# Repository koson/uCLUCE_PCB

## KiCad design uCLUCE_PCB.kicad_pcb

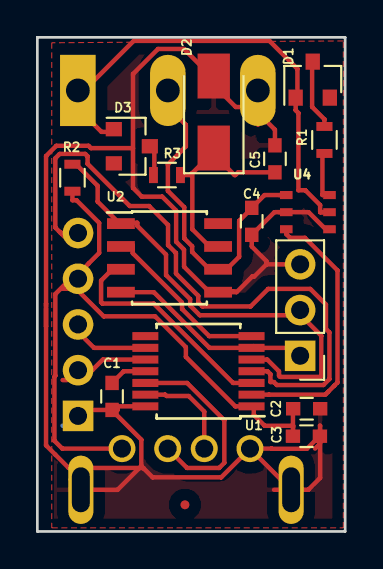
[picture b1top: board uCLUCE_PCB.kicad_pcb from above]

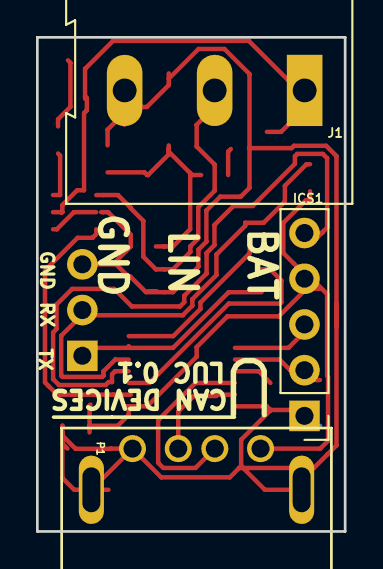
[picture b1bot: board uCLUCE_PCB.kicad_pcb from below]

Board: 2 copper layers, 17.1 x 27.5 mm, 19 parts (4 on the bottom side), 19 nets.

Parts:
C1: 0.47u; C_0603
C2: 470n; C_0603
C3: 100n; C_0603
C4: 220p; C_0603
C5: 1u; C_0603
D1, D3: SMBD914E6327HTSA1; D_SOT-23_ANK
D2: D_Schottky_Small; D_SMA
ICS1: Conn_01x05; Pin_Header_Straight_1x05_Pitch2.54mm
J1: Screw_Terminal_01x03; AK300-3
P1: USB_A; USB_A_DS1097R
P2: UART_TTL; Pin_Header_Straight_1x03_Pitch2.54mm
R1: 1k; R_0603
R2: 4,7k; R_0603
R3: 50; R_0603
U1: PIC16F1455-I/ST; TSSOP-14_4.4x5mm_Pitch0.65mm
U2: MCP2003B-E/SN; SOIC-8_3.9x4.9mm_Pitch1.27mm
U3: fiducial; FICUCIAL_MIN
U4: DG468; TSOP6

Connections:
+5V: C2.2, C3.2, ICS1.4, P1.1, R2.2, U1.1
+BATT: D1.2, D3.2, J1.1, U4.5
/MCLR: ICS1.5, U1.4
GND: C1.1, C2.1, C3.1, C4.2, C5.2, D2.2, ICS1.1, J1.3, P1.4, P1.5, P2.3, U1.14, U2.5, U4.2, U4.4
unnamed: C1.2, U1.11
unnamed: C4.1, J1.2, U2.6, U4.1
unnamed: C5.1, D2.1, R3.1, U2.7
unnamed: D1.1, R1.1
unnamed: D3.1, R3.2
unnamed: ICS1.2, U1.10
unnamed: ICS1.3, U1.9
unnamed: P1.2, U1.12
unnamed: P1.3, U1.13
unnamed: P2.1, U1.6, U2.4
unnamed: P2.2, R2.1, U1.5, U2.1
unnamed: R1.2, U4.6
unnamed: U1.2, U4.3
unnamed: U1.3, U2.3
unnamed: U1.7, U2.2

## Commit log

2017-10-13 Init
2017-10-16 Coponents add
2017-10-16 Route
2017-10-17 diodes add
2017-10-18 Footprint update
2017-10-18 gerber generation
2017-11-27 Fixed USB Layout
2017-12-04 Flip LIN RX/TX
2017-12-13 Analog sw
2022-10-06 update to Kicad 6
